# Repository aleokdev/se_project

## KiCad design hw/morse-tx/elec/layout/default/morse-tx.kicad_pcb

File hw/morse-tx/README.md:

# morse-tx

Wooohooo a new package!

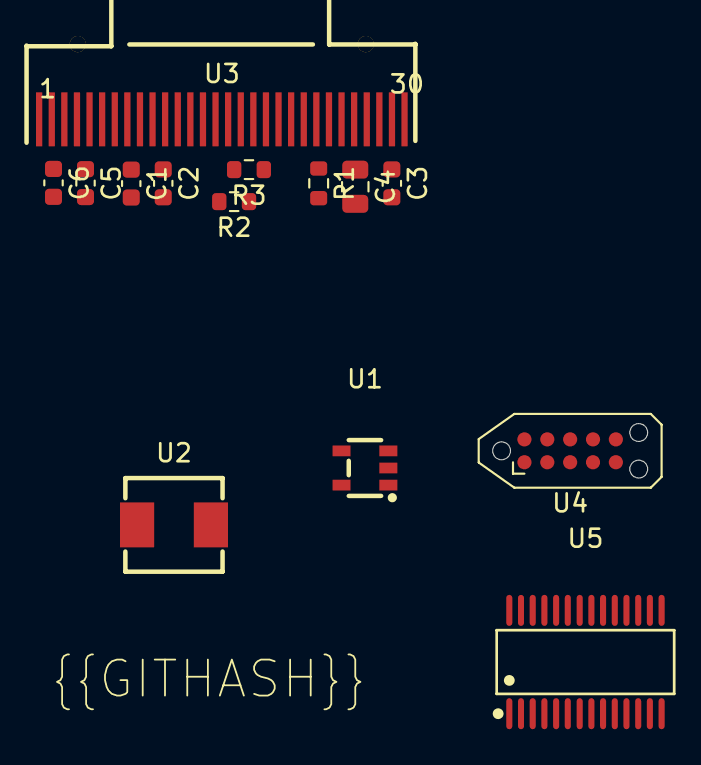
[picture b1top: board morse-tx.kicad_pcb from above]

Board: 2 copper layers, 14 parts (0 on the bottom side), 19 nets, no tracks yet.

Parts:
C1, C2, C5, C6: Multilayer Ceramic Capacitors MLCC - SMD/SMT 1uF 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; C0603
C3: Multilayer Ceramic Capacitors MLCC - SMD/SMT 2.2u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; C0603
C4: C0805
R1: Chip Resistor - Surface Mount 560KOhms ±5% 1/10W 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; R0603
R2, R3: Chip Resistor - Surface Mount 4.7KOhms ±5% 1/10W 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; R0603
U1: SOT-23-5_L3.0-W1.7-P0.95-LS2.8-BR
U2: IND-SMD_L5.4-W5.2_FXL0530
U3: OLED_0.96-30P-P0.70-12864
U4: Tag-Connect_TC2050-IDC-NL_2x05_P1.27mm_Vertical
U5: TSSOP-28_L9.7-W4.4-P0.65-LS6.4-BL

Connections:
c1n: C5.2, U3.5
c1p: C5.1, U3.4
c2n: C6.2, U3.3
c2p: C6.1, U3.2
gnd: C1.2, C2.2, C3.2, C4.2, R1.2, U1.2, U3.8, U3.10, U3.12, U3.13, U3.15, U3.16, U3.17, U3.29, U4.9, U5.28
iref: R1.1, U3.26
n_c__gnd_: U3.1, U3.30
reset: U4.10, U5.24
scl: R2.1, U3.18
sda: R3.1, U3.19, U3.20
sw: U1.5, U2.1
tck: U4.7, U5.6
tdi: U4.1, U4.3, U5.23
test: U4.8, U5.25
tms: U4.5, U5.7
vcc: C1.1, C2.1, R2.2, R3.2, U1.4, U2.2, U3.6, U3.9, U3.11, U4.2, U4.4, U5.1
vcc-1: U1.1, U1.3
vcc-2: C3.1, U3.28
vcomh: C4.1, U3.27

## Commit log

2024-01-19 Working morse translation
2024-01-19 Add buzzer signal
2024-01-19 Format document
2024-01-20 Starting new letters
2024-01-20 Clean up `translate_morse`
2024-01-20 Clean up, fix rotary encoder rotation
2024-01-20 Add settings menu, font + screen shenanigans
2024-01-20 Reorganization
2024-01-20 Reformat
2024-01-20 Working tone setting
2024-01-21 Reorganize & clean up
2024-01-21 Misc improvements
2024-01-21 Fix formatting & clang-format file
2024-01-21 Rewrite morse transmission
2024-01-21 Dah time setting, improve scroll speed
2024-01-22 Tone volume (partial)
2024-01-22 New board: New pins
2024-01-22 Output selection setting
2024-01-22 Fix volume drawing
2024-01-23 Fix some bugs
2024-01-23 Morse table menu
2024-01-23 Move morse display position
2024-01-25 Low power mode
2024-01-25 Fix LPM time
2024-01-26 Create a selection menu
2024-01-26 Play tone while changing its value
2024-01-26 Saving and loading settings
2024-01-26 Move IO setup, simplify & document clock setup
2024-01-26 Fix volume setting
2024-01-27 Misc fixed & improvements
2024-01-27 Startup sound
2024-01-28 Add schematic folder
2024-01-29 Some display optimization
2024-01-30 Morse guide menu
2024-01-30 Clean up & refactor tx & guide menus
2024-01-30 Show stats on guide menu
2024-01-31 Faster clearPage
2024-01-31 Clean up i2c/ssd1306 library
2024-01-31 Display driver fixes, turn on screen after draw
2024-01-31 Fix warning
2024-01-31 Add morse backspace
2024-02-01 Misc improvements & fixes
2024-02-01 Remove `in_low_power_mode` from `State`
2024-02-01 Erase redraw functions from menus header
2024-02-01 Clean up
2024-02-01 Formatting
2024-02-01 Build in release
2024-02-02 Documentation, fixes, clean up
2024-02-03 Fix: Show Z translation on morse table
2024-02-03 Fix: Save settings properly
2024-02-03 More volatile shenanigans
2024-02-03 5x faster I2C
2024-02-03 Reorder settings menu internals
2024-02-03 Morse tx clean-up
2024-02-04 Move last_menu to menu state
2024-02-11 Create atopile project (internal build error)
2024-02-18 Partial commit
2024-02-18 Add new schematics
